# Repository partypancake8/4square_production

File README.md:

# 4square

<p align="center"></p>

4square is a small desk clock built around four 0.96 in OLED panels in a 2x2
grid: hours top-left, minutes top-right, weekday and date along the bottom. It
runs on an ESP32-C3 SuperMini on a custom 74 x 74 mm board, in a 3D-printed
shell with a laser-cut clear acrylic back that shows the board. To protect the
panels from burn-in, every pixel goes through one function that applies a pixel
shift and a brightness cap, and a prover on your PC checks every screen the
firmware can draw before an image ships.

| | |
|---|---|
| MCU | ESP32-C3 SuperMini (RISC-V, WiFi, native USB-C) |
| Displays | four 0.96 in 128x64 SSD1306 OLEDs, all white, behind a PCA9548A I2C mux |
| Timekeeping | DS3231 RTC with CR2032 backup |
| Sensors | SHT31 temperature and humidity, phototransistor light sensor |
| Indicators | three addressable RGB LEDs in a vertical column |
| Input | four buttons: MODE, SET, UP, DOWN |
| Settings storage | 24LC256 EEPROM, wear-levelled, survives reflashing |
| Board | custom 74 x 74 mm, 2 layer, rev O, JLCPCB assembly plus a hand-solder kit |
| Case | rev 5 PETG prints plus a rev 6 laser-cut 3 mm acrylic back with engraving, about 79 x 79 mm |
| Power | USB-C, either the rear port or the SuperMini's own |

This repository has everything needed to build one: firmware, a prebuilt image,
the board's manufacturing files and the case.

## Repository layout

    firmware/               the firmware (Arduino sketch + src/) and build.sh
    release/                prebuilt demo image, flash.sh, checksums
    tools/layoutcheck/      the layout prover (runs on your PC, not the board)
    tools/ledcheck/         the LED animation prover
    tools/pageshot/         renders any page to a PNG on your PC
    tools/secretsweep/      lists the credential literals a build must not leak
    hardware/               board notes, gerbers, BOM, CPL, kit list, board PDF, KiCad file
    case/                   printable STLs, the acrylic back DXF, build123d sources
    docs/BUILD.md           assembly, step by step
    docs/media/             photos and renders
    LICENSE                 MIT

## Hardware

<table>
<tr>
<td align="center"><br><sub>Front, with the four screens (KiCad render)</sub></td>
<td align="center"><br><sub>Back, the side the acrylic shows (KiCad render)</sub></td>
</tr>
</table>

The board is two layers, 74 x 74 mm. The screens plug into sockets on the
front; everything else is on the back. Surface-mount parts are all on one side
so the board can be ordered as JLCPCB Economic assembly, and a short kit of
through-hole parts (the EEPROM socket, axial resistors, buttons, battery clip,
rear USB-C and headers) is soldered by hand. The axial resistors are there on
purpose: through the acrylic back they read as a colour-band ladder.

- [`hardware/HARDWARE.md`](hardware/HARDWARE.md): every part, the pin map, the
  mux channel for each screen, and two silkscreen errors on rev O worth
  knowing before you solder.
- [`hardware/ORDER-NOTES.md`](hardware/ORDER-NOTES.md): placing the JLCPCB
  order and checking the placement preview.
- `hardware/4square-revO-gerbers.zip`, `bom.csv`, `cpl.csv`, `kit-bom.csv`: the
  order package as it was sent.
- `hardware/4square-revO-board.pdf`: plots of every copper and silk layer.
- `hardware/kicad/4square-revO.kicad_pcb`: the KiCad 9 board file.

## Case

<table>
<tr>
<td align="center"><br><sub>The acrylic back, engraved on the inside face</sub></td>
<td align="center"><br><sub>The screens lit with the clock face</sub></td>
</tr>
</table>

Front to back: a printed shell with a pocket for each screen, a two-piece
retainer that holds the screens flat against the glass, the board on the
shell's corner bosses, a printed standoff frame, and a 3 mm clear acrylic back.
Four M3 x 16 self-tapping screws hold it together. A printed back can replace
the acrylic and frame if you have no laser cutter.

The acrylic is engraved on its inside face, so the DXF is drawn mirrored,
inside-face-up. [`case/README.md`](case/README.md) has the print settings,
orientation, and the cutter notes; [`docs/BUILD.md`](docs/BUILD.md) has the
assembly order.

## Firmware

### Buttons

Each button owns a page, and pressing the same button again cycles that
page's variants, so there is no menu to navigate.

| button | page | press it again |
|---|---|---|
| MODE | clock | next clock style: outline, filled, then five more faces each in outline and filled (12 in all) |
| SET | readings: temperature, network, uptime, light | second set: humidity, IP, ambient light, day or night |
| UP | stopwatch: minutes, seconds, state, hours | starts or resumes it; DOWN on this page pauses, then clears |
| DOWN | animations | first press starts the showreel; second press drops to a shuffled roster of the 48x48 animations |

Long press (600 ms): MODE toggles the status LEDs; SET opens the settings
page. On the settings page SET moves to the next item, UP and DOWN change it,
MODE leaves. It times out back to the clock after 30 s.

The stopwatch replaced an earlier stock ticker page. It runs on `millis()`,
keeps counting while you look at other pages, and UP always brings it back.
Minutes carry into the hours panel.

The showreel is a 66 second loop that treats the 2x2 as one scene: a giant
clock, a walking figure crossing both panels of a row, live sensor readings, a
forecast with animated skies, demo market quotes and a heartbeat across all
four panels.

Settings items: LIGHT SENS (how strongly auto-dim responds), TEMP UNIT (C or F,
global), AUTO OFF (a daily screens-off window), SLEEP AT and WAKE AT (its
times, in 15 minute steps). The panels dim from 22:30 to 07:00 and, by
default, switch off entirely from 23:30 to 06:30. Settings already stored in the
EEPROM win over these defaults, and AUTO OFF on the settings page turns the
schedule off.

Until SW1-SW4 are fitted, the buttons can also be pressed over serial (`B0` to
`B3`, `B0L` to `B3L` for a long press).

### Designed for panel lifetime

These panels are rated around 10,000 hours, and a clock runs 8,760 hours a
year, so burn-in is the most likely way this clock fails. The firmware limits it
in six ways:

- **One route to the glass.** `firmware/foursquare/src/screens/display.cpp` is
  the only file that can write to a panel; the four `Adafruit_SSD1306` objects
  have internal linkage there. Every other drawing routine is handed a
  `GFXcanvas1` in RAM, and `disp_commit()` blits canvas to panel, applying the
  pixel shift, the brightness cap and the night policy on the way. Because a
  new clock face has no other route to a panel, it always gets the shift and
  the cap.
- **Pixel shift.** The image walks a serpentine tour inside a 6 px margin,
  spending exactly equal time at every offset.
- **Outline digits by default.** Hollowing a large digit cuts it from about 800
  lit pixels to about 170.
- **Brightness is a lifetime setting.** Contrast, precharge and VCOMH are set
  together, capped by day and hard-limited at night; inverted display is never
  used.
- **Dark when nobody is looking.** A night window dims, a daily window switches
  the panels off, and a button press inside either wakes them for 30 s.
- **Idle LEDs are dark**, and every held LED state has a time budget, because
  the clock lives in a bedroom.

### The layout prover

    tools/layoutcheck/build.sh            # shipping build's screens
    DEMO=1 tools/layoutcheck/build.sh     # demo build's screens

It compiles the firmware's own `faces.cpp`, `pages.cpp`, `anim.cpp` and
`defaults.cpp` on your PC against the Adafruit_GFX library and renders
every screen the firmware can draw (about 244,000 of them, including every
stopwatch reading). It fails if any pixel is claimed by two elements, if any ink
falls outside the safe area `x[6..121] y[6..57]` that the pixel shift needs, or
if an animation has a blank or discontinuous frame, and it warns on crowding and
fill factor. Overlap is found by having the firmware mark element boundaries
with `ELEM("name")`; on the host that hook snapshots and clears the canvas, so
the pairwise AND of the element bitmaps is the overlap exactly. On the device
the hook is null. The prover self-tests against planted bugs before it reports.
It needs `g++` and Python with Pillow. `tools/ledcheck/build.sh` does the same
job for the LED animations.

### Settings storage

Settings live in the 24LC256 EEPROM at 0x50, not in the ESP32's flash, so a
firmware flash, a partition change or a full chip erase never loses them. They
are stored as a wear-levelled ring of 128 records, each with a sequence number
and CRC: a torn write costs the last change, not the whole configuration.
Everything read back is range-clamped. Serial `F` factory-resets the ring.

### Serial

115200 baud, native USB CDC. `?` report, `P` settings, `T Y M D h m s` set the
clock, `Z` clear the RTC oscillator-stop flag, `S` rescan screens, `R [n]`
rotate, `D [n]` pin contrast, `I` identify, `F` factory reset, `B0` to `B3`
press MODE/SET/UP/DOWN, `B0L` to `B3L` hold them, `W` stopwatch state. The
board does not reset on DTR/RTS, so reopening the port does not show the boot
banner; `?` prints the state instead.

## Flash

The quickest way to see it run is the prebuilt demo image in `release/`. You
need `esptool` (`pip install esptool`) and a USB-C cable. The SuperMini is
native USB: it appears as `/dev/ttyACM0` on Linux or `/dev/cu.usbmodem*` on
macOS.

    git clone https://github.com/partypancake8/4square_production
    cd 4square_production/release
    ./flash.sh

or by hand:

    esptool --chip esp32c3 --port /dev/ttyACM0 --baud 921600 write_flash --flash_mode dio --flash_freq 80m --flash_size 4MB 0x0 4square-demo-merged.bin

`4square-demo-merged.bin` is the whole flash (bootloader, partition table and
app) and goes at `0x0`. If you only want the app slot, `4square-demo.bin` goes
at `0x10000` with `bootloader.bin` at `0x0`, `partitions.bin` at `0x8000` and
`boot_app0.bin` at `0xe000`. `SHA256SUMS` covers all of them.

If esptool cannot find the chip, hold BOOT on the SuperMini while plugging it
in, then run the command again. Unplug and replug after flashing; the board
boots straight into the clock.

The demo image has no WiFi code in it at all, so it never joins a network and
never needs credentials. Time comes from the DS3231; set it over serial if the
clock chip has never been set.

### Release

**The binaries in `release/` predate the stopwatch.** They were built from the
firmware at commit `c80900a` of this repository, where UP is still the market
ticker page. Everything else (clock faces, showreel, settings, auto-off) matches
the current source. To get the stopwatch, build from source as below.

## Build

There are two builds of the same source:

| build | flag | radio | needs secrets.h | what it is for |
|---|---|---|---|---|
| demo | `-DDEMO_BUILD` | none compiled in | no | showing the clock to people: showreel, Fahrenheit, brighter panels |
| full | (none) | WiFi + OTA | yes | running it at home on your own network |

Install [arduino-cli](https://arduino.github.io/arduino-cli/), the ESP32 core
and the four libraries the sketch uses:

    arduino-cli config init
    arduino-cli config add board_manager.additional_urls https://espressif.github.io/arduino-esp32/package_esp32_index.json
    arduino-cli core update-index
    arduino-cli core install esp32:esp32
    arduino-cli lib install "Adafruit GFX Library" "Adafruit SSD1306" "Adafruit BusIO" "Adafruit NeoPixel"

The current source builds with esp32 core 3.3.7, Adafruit GFX 1.12.6, SSD1306
2.5.16, BusIO 1.17.4 and NeoPixel 1.15.4.

Board and partition scheme:

    FQBN: esp32:esp32:esp32c3:CDCOnBoot=cdc,PartitionScheme=no_fs

`CDCOnBoot=cdc` routes Serial to the SuperMini's native USB.
`PartitionScheme=no_fs` gives two 2 MB app slots with OTA and no filesystem;
settings live in the external EEPROM. Changing the partition scheme needs a USB
flash; OTA cannot rewrite the partition table.

Then:

    firmware/build.sh demo                       # demo image, no secrets needed
    firmware/build.sh full                       # full image, needs src/secrets.h
    firmware/build.sh demo --upload /dev/ttyACM0 # build and flash in one go

`build.sh` runs the layout prover first, for the variant you asked for, and
stops if it fails, so every image passes the prover before it ships
(`--no-check` skips it). It compiles with `--jobs 4` and `--clean`, and passes
`-ffile-prefix-map` so the binary carries no local paths. Output goes to
`firmware/out/<variant>/`: `foursquare.ino.bin` (app) and
`foursquare.ino.merged.bin` (whole flash).

By hand, the demo flag is one compiler define:

    tools/layoutcheck/build.sh
    arduino-cli compile --fqbn esp32:esp32:esp32c3:CDCOnBoot=cdc,PartitionScheme=no_fs \
      --build-property "compiler.cpp.extra_flags=-DDEMO_BUILD" \
      --jobs 4 --output-dir out firmware/foursquare

Use `compiler.cpp.extra_flags`, not `build.extra_flags`: overriding the latter
drops the core's own defines and the SSD1306 library stops compiling. Leave the
define off for the full build. Everything the demo flag changes is inside
`#ifdef DEMO_BUILD` and listed in one place, `firmware/foursquare/src/demo.h`.

### WiFi (full build only)

    cp firmware/foursquare/src/secrets.h.example firmware/foursquare/src/secrets.h

and fill in your SSID and password (two networks are tried in turn; use the
same one twice if you have one) and the SHA256 of your OTA password
(`echo -n 'your-password' | sha256sum`). `secrets.h` is gitignored. The full
build refuses to compile without it; the demo build does not read it.

The credentials are declared `static const` inside `#ifndef DEMO_BUILD`, and
the OTA password is only stored as a digest, so a demo image contains no
credential. `tools/secretsweep/literals.sh secrets.h` prints the values a built
image should be grepped for before you share it. Once the full build is running,
OTA updates go to host `foursquare-revo` with `espota.py -a <your OTA password>`.

## Photos

<table>
<tr>
<td align="center"><br><sub>The rev O board seated in the case, back removed</sub></td>
<td align="center"><br><sub>The assembled case (render)</sub></td>
</tr>
<tr>
<td align="center"><br><sub>Dimmed for the night window</sub></td>
<td align="center"><br><sub>On the desk</sub></td>
</tr>
<tr>
<td align="center"><br><sub>The market ticker page from the earlier firmware, since replaced by the stopwatch</sub></td>
<td align="center"><br><sub>One of the four M3 x 16 self-tapping screws (render)</sub></td>
</tr>
<tr>
<td align="center"><br><sub>The first prototype, before the custom board</sub></td>
<td align="center"><br><sub>The hand-wired perfboard version</sub></td>
</tr>
</table>

An MP4 of the exploded view is at
[`docs/media/4square-exploded.mp4`](docs/media/4square-exploded.mp4).

## License

MIT, see [`LICENSE`](LICENSE).

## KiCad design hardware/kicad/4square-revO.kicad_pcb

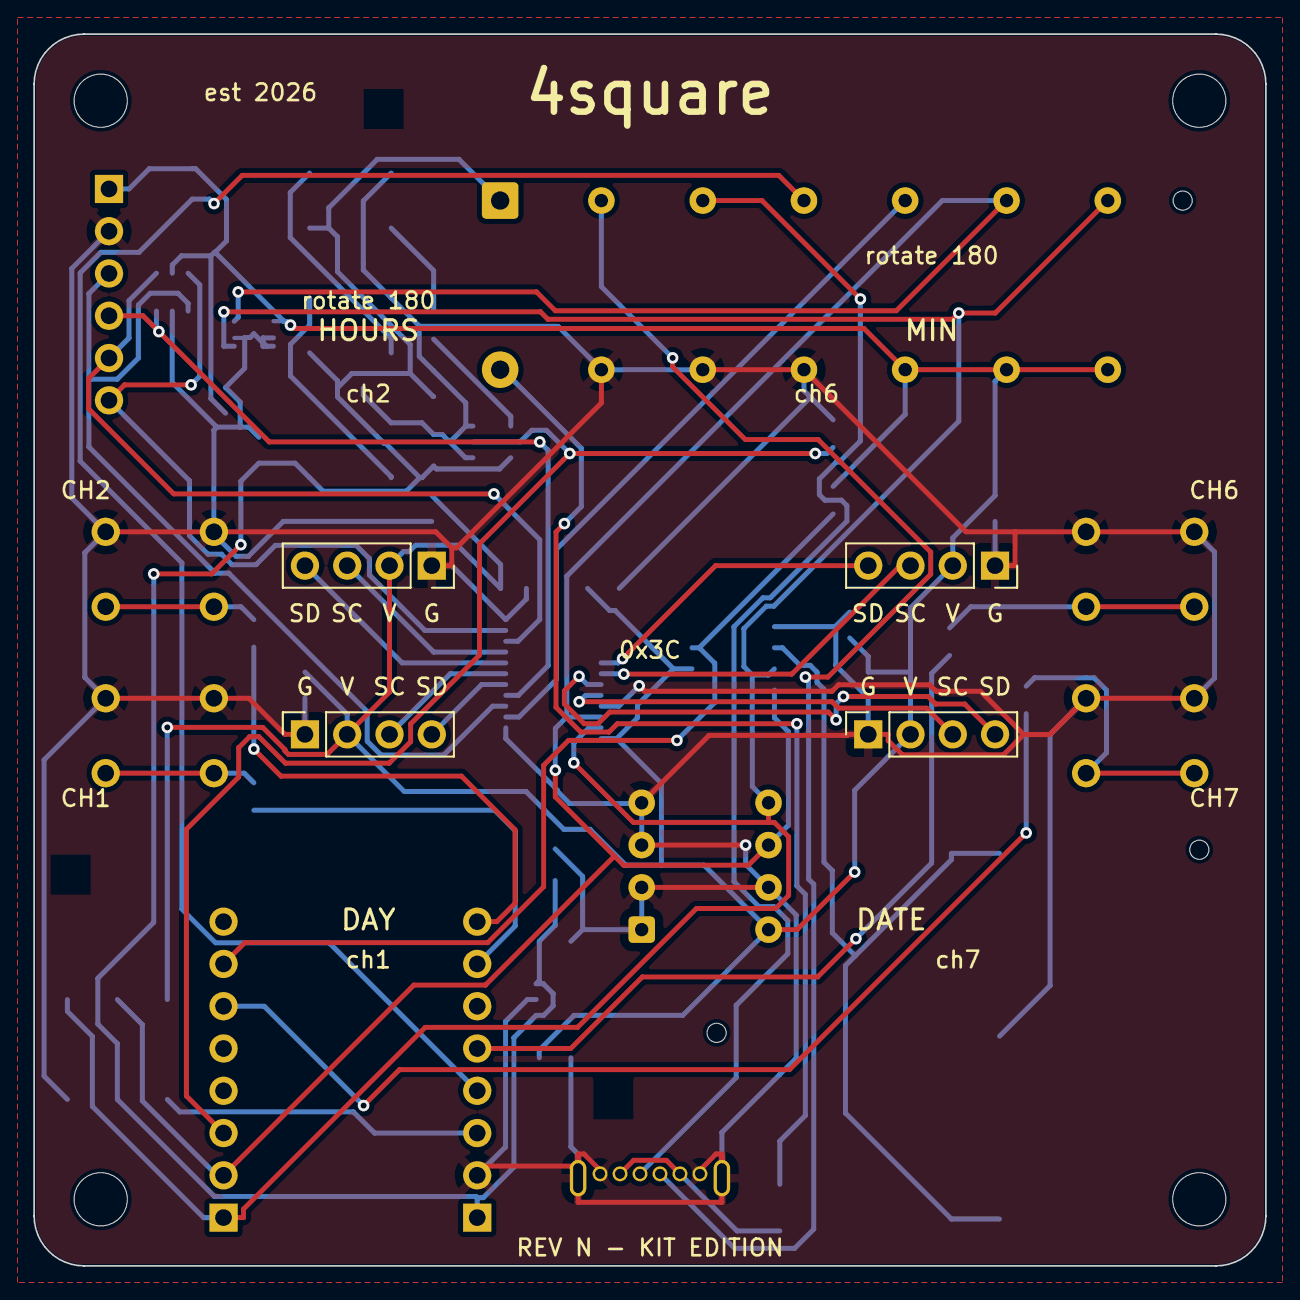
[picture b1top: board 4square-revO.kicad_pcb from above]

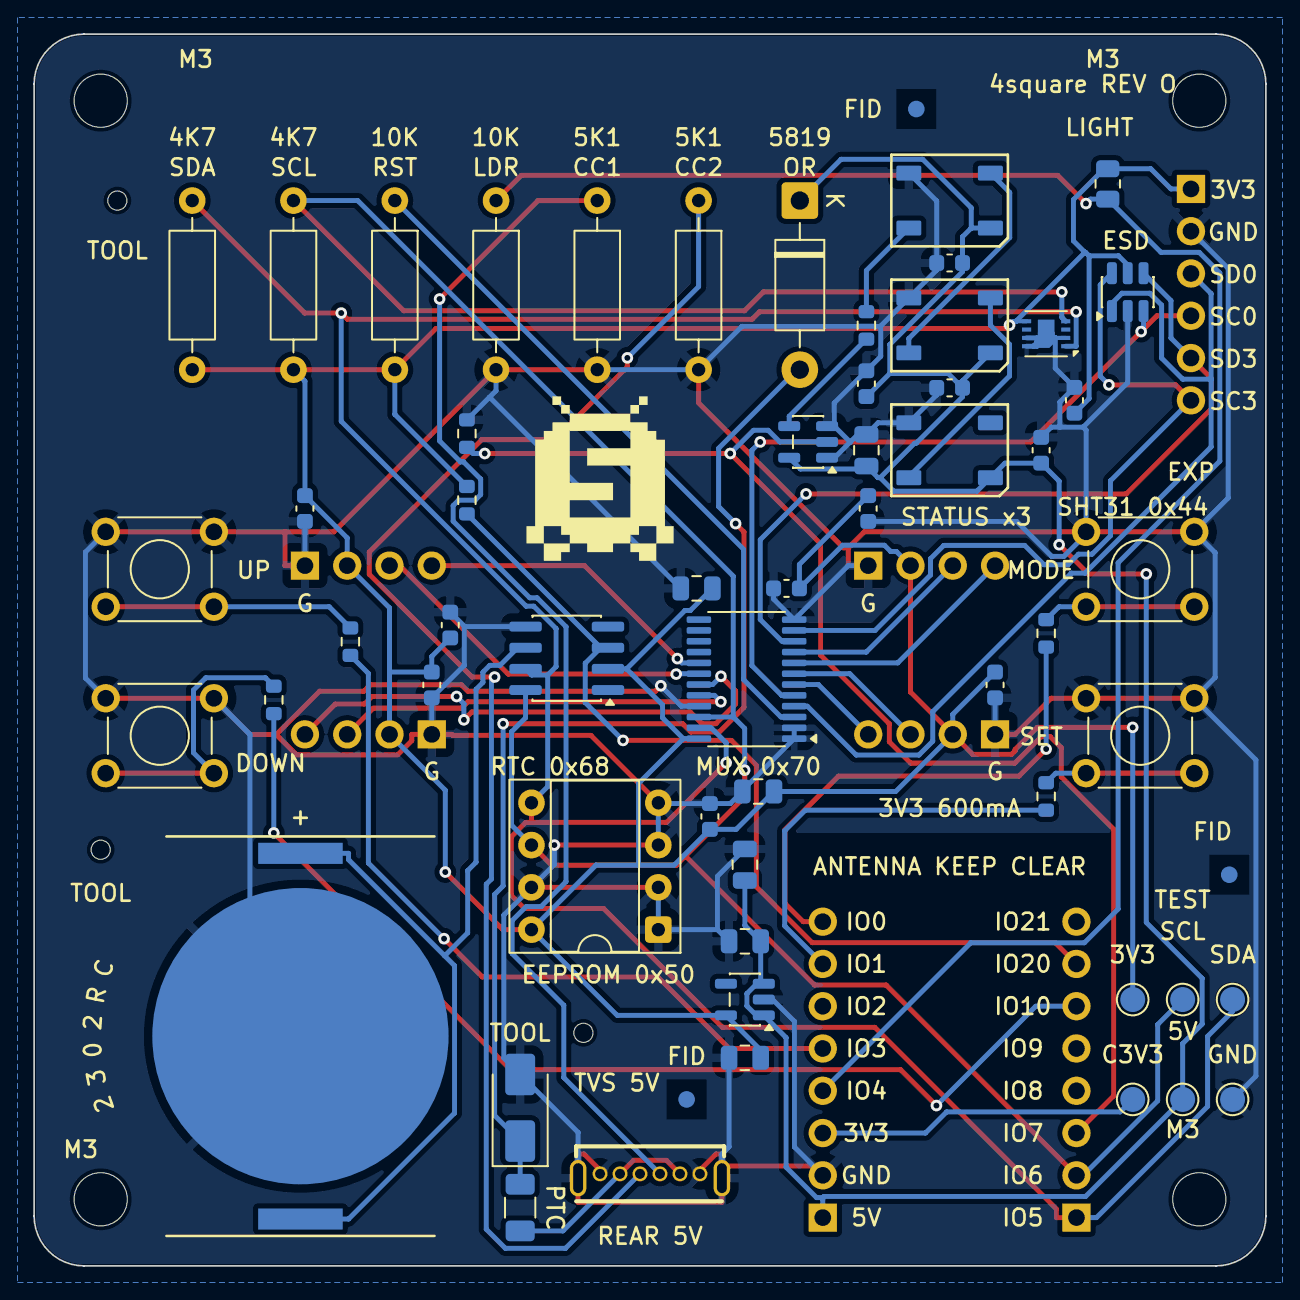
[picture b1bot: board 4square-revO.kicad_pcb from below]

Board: 2 copper layers, 74.0 x 74.0 mm, 74 parts (66 on the bottom side), 39 nets.

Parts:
BT1: BatteryHolder_Keystone_3034_1x20mm
C1, C5, C6, C7, C8, C10, C11, C12, C13, C14, C16, C17: C_0603_1608Metric
C2, C3, C4, C9, C15, C18: C_0805_2012Metric
D1: D_DO-41_SOD81_P10.16mm_Horizontal
D2, D4, D5: LED_WS2812B_PLCC4_5.0x5.0mm_P3.2mm
D3: D_SMA
F1: Fuse_1206_3216Metric
FID1, FID2, FID3: Fiducial_1mm_Mask2mm
H1, H2, H3, H4: MountingHole_3.2mm_M3
J1, J2, J3, J4: PinSocket_1x04_P2.54mm_Vertical
J5, J6: PinSocket_1x08_P2.54mm_Vertical
J8: PinSocket_1x06_P2.54mm_Vertical
J9: USB-TH_TYPE-C-6P-LCH10.0
R1, R2, R3, R4, R5, R6: R_Axial_DIN0207_L6.3mm_D2.5mm_P10.16mm_Horizontal
R7: R_0805_2012Metric
R8, R9, R10, R11, R12, R13, R14: R_0603_1608Metric
SW1, SW2, SW3, SW4: SW_TH_Tactile_Omron_B3F-100x
TH1, TH2, TH3: ToolingHole_1.152mm
TP1, TP2, TP3, TP4, TP5, TP6: TestPoint_Pad_D1.5mm
U1: TSSOP-24_4.4x7.8mm_P0.65mm
U2, U6: SOT-23-5
U3: DIP-8_W7.62mm_Socket
U4: SOIC-8_3.9x4.9mm_P1.27mm
U5: Sensirion_DFN-8-1EP_2.5x2.5mm_P0.5mm_EP1.1x1.7mm
U7: SOT-23-6

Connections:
+3V3: C1.1, C2.1, C4.1, C5.1, C6.1, C7.1, C8.1, C9.1, C11.1, C12.1, C13.1, J1.2, J2.2, J3.2, J4.2, J8.1, R1.2, R2.2, R3.2, R7.2, R14.2, TP3.1, U1.24, U2.5, U3.8, U4.2, U5.5, U7.5
+5V_VBUS: C3.1, C10.1, C14.1, C15.1, C16.1, C17.1, C18.1, D1.1, D2.1, D4.1, D5.1, J5.1, TP4.1, U2.1, U2.3, U6.5
BTN1: R8.2, SW1.1, SW1.3
BTN2: R9.2, SW2.1, SW2.3
BTN3: R10.2, SW3.1, SW3.3
BTN4: R11.2, SW4.1, SW4.3
C3_3V3: J5.3, TP6.1
CC1: J9.A5, R5.1
CC2: J9.B5, R6.1
GND: BT1.2, C1.2, C2.2, C3.2, C4.2, C5.2, C6.2, C7.2, C8.2, C9.2, C10.2, C11.2, C12.2, C13.2, C14.2, C15.2, C16.2, C17.2, C18.2, D2.3, D3.2, D4.3, D5.3, J1.1, J2.1, J3.1, J4.1, J5.2, J8.2, J9.7, J9.8, J9.A12, J9.B12, R4.2, R5.2, R6.2, R13.2, SW1.2, SW1.4, SW2.2, SW2.4, SW3.2, SW3.4, SW4.2, SW4.4, TP5.1, U1.1, U1.2, U1.12, U1.21, U2.2, U3.1, U3.2, U3.3, U3.4, U3.7, U4.5, U5.2, U5.7, U5.8, U5.9, U6.1, U6.3, U7.2
GPIO0: J5.8, R8.1
GPIO1: J5.7, R9.1
GPIO3: J5.5, R10.1
GPIO7: J6.3, R13.1, U6.2
GPIO10: J6.6, R11.1
GPIO20: J6.7, R14.1, U4.3
LDR_SENSE: J5.4, R4.1, R7.1
LED_CH1: D2.2, D4.4
LED_CH2: D4.2, D5.4
LED_DIN: D2.4, R12.2
LED_DRV: R12.1, U6.4
MUX_nRESET: R3.1, U1.3
SCL: J6.2, R2.1, TP2.1, U1.22, U3.6, U4.8, U5.4
SCL0: J8.4, U1.5, U7.3
SCL1: J3.3, U1.7
SCL2: J1.3, U1.9
SCL3: J8.6, U1.11, U7.6
SCL6: J2.3, U1.18
SCL7: J4.3, U1.20
SDA: J6.1, R1.1, TP1.1, U1.23, U3.5, U4.7, U5.1
SDA0: J8.3, U1.4, U7.1
SDA1: J3.4, U1.6
SDA2: J1.4, U1.8
SDA3: J8.5, U1.10, U7.4
SDA6: J2.4, U1.17
SDA7: J4.4, U1.19
VBAT: BT1.1, U4.6
VBUS_PROT: D1.2, D3.1, F1.2
VBUS_REAR: F1.1, J9.A9, J9.B9

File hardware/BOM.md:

# 4square bill of materials, one clock

Everything that goes into one finished clock. The machine-readable files are
`bom.csv` (JLCPCB assembly) and `kit-bom.csv` (the LCSC hand-solder kit).

## Assembled by JLCPCB (bottom side, from `bom.csv`)

| qty | part | refs | LCSC |
|---|---|---|---|
| 1 | PCA9548APW I2C mux, TSSOP-24 | U1 | C130026 |
| 1 | AP2112K-3.3 LDO, SOT-23-5 | U2 | C51118 |
| 1 | DS3231MZ RTC, SO-8 | U4 | C107410 |
| 1 | SHT31-DIS-B temperature and humidity, DFN-8 | U5 | C80862 |
| 1 | SN74AHCT1G125 buffer, SOT-23-5 | U6 | C7484 |
| 1 | SRV05-4 ESD array, SOT-23-6 | U7 | C85364 |
| 3 | GL5050RGB01H-W addressable RGB LED | D2, D4, D5 | C51933368 |
| 1 | SMAJ5.0A TVS, SMA | D3 | C87074 |
| 1 | 750 mA polyfuse, 1206 | F1 | C371166 |
| 1 | PT17-21C phototransistor, 0805 | R7 | C100090 |
| 4 | 1k 0603 | R8-R11 | C21190 |
| 1 | 470R 0603 | R12 | C23179 |
| 2 | 10k 0603 1% | R13, R14 | C25804 |
| 12 | 100n 0603 | C1, C5-C8, C10-C14, C16, C17 | C14663 |
| 4 | 10u 0805 | C2-C4, C18 | C15850 |
| 2 | 22u 0805 | C9, C15 | C45783 |

## Hand-soldered kit (from `kit-bom.csv`)

| qty | part | refs | LCSC |
|---|---|---|---|
| 1 | Keystone 3034 CR2032 holder | BT1 | C5199422 |
| 1 | USB-C receptacle, 6 pin, power only | J9 | C5187470 |
| 1 | 1N5819 Schottky, DO-41 | D1 | C110032 |
| 2 | 4.7k 1/4 W axial | R1, R2 | C173023 |
| 1 | 10k 1/4 W axial | R3 | |
| 1 | 1k 1/4 W axial | R4 | |
| 2 | 5.1k 1/4 W axial | R5, R6 | |
| 4 | 6x6 mm tactile switch | SW1-SW4 | C7528713 |
| 1 | 24LC256 EEPROM, DIP-8 | U3 | C19193485 |
| 1 | DIP-8 socket | U3 | C2874007 |
| 1 | 1x40 female header strip, cut to 4x 1x4, 2x 1x8, 1x 1x6 | J1-J6, J8 | C9811 |

## Modules and mechanical

| qty | part |
|---|---|
| 1 | ESP32-C3 SuperMini |
| 4 | 0.96 in SSD1306 128x64 I2C OLED module, all white, 4 pin |
| 1 | CR2032 cell |
| 4 | M3 x 16 mm self-tapping screws |
| 1 | 74 x 74 mm piece of 3 mm cast acrylic, laser cut (or the printed back) |
| about 55 g | PETG for the shell, retainer halves and standoff frame |
